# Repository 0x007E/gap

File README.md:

# `GAP` - GamePad (HTLboy)

The `GAP` project is based on a pcb with an [ATmega3208/ATmega4808](#additional-information) and is extended with two [Matrix LED Displays](https://github.com/0x007e/mad). It can be used as controller for games and graphical things. The `GAP` has 8 buttons (1 Cross `[4]`, A & B `[2]`, Select `[1]` and Start `[1]`), 4 LEDs, a potentiometer to control the volume and a built in `UPDI` programmer for the pad itself and the connected displays. Data for displays is sent over `SPI`. The `GAP` also implements a battery controller for [LiPo Batteries](#additional-information). They can be charged over USB. The battery can drive the system for about ~5 hours. There is also a `TWI` interface to load games from an `EEPROM` into the system.

| Experience | Level |
|:------------|:-----:|
| Soldering   |  |
| Mechanical  |  |
| Software    |  |

# Downloads

| Type      | File               | Description              |
|:---------:|:------------------:|:-------------------------|
| Schematic | [pdf](https://github.com/0x007E/gap/releases/latest/download/schematic.pdf) / [cadlab](https://cadlab.io/project/29666/main/files) | Schematic files |
| Board | [pdf](https://github.com/0x007E/gap/releases/latest/download/pcb.pdf) / [cadlab](https://cadlab.io/project/29666/main/files) | Board file |
| Drill | [pdf](https://github.com/0x007E/gap/releases/latest/download/drill.pdf) | Drill file |
| PCB | [zip](https://github.com/0x007E/gap/releases/latest/download/kicad.zip) / [tar](https://github.com/0x007E/gap/releases/latest/download/kicad.tar.gz) | KiCAD/Gerber/BoM/Drill files |
| Mechanical | [zip](https://github.com/0x007E/gap/releases/latest/download/freecad.zip) / [tar](https://github.com/0x007E/gap/releases/latest/download/freecad.tar.gz) | FreeCAD/Housing and PCB (STEP) files     |
| Display Firmware | [zip](https://github.com/0x007E/mad/releases/latest/download/firmware.zip) / [tar](https://github.com/0x007E/mad/releases/latest/download/firmware.tar.gz) | Firmware for ATtiny406/ATtiny1606 (Display) |
| Demo Firmware | [zip](https://github.com/0x007E/gap/releases/latest/download/firmware-demo.zip) / [tar](https://github.com/0x007E/gap/releases/latest/download/firmware-demo.tar.gz) | Test application for ATmega3208/ATmega4808 |

# Hardware

There are two parts of the hardware. The pcb (`GAP` + 2x`MAD`) and the housing. The pcb is created with [KiCAD](#additional-information) and the housing with `FreeCAD`. The software is programmed with [Microchip (Atmel) Studio](#additional-information). All files are built with `github actions` so that they are ready for a production environment. The housing is printed with a 3D-printer (`Dremel 3D40`).

## PCB

The circuit board is populated on both sides (Top, Bottom). The best way for soldering the `SMD` components is within a vapor phase soldering system and for the `THT` components with a standard soldering system.

### Top Layer

### Bottom Layer

## Mechanical

The housing has a tolerance of `0.2mm` on each side of the case. So the pcb should fit perfectly in the housing. The tolerance can be modified with `FreeCAD` in the `Parameter` Spreadsheet.

### Assembled

#### Exploded

# Programming/Setup

For programming the `GAP` is necessary to power the system with `5V` over the USB jack. The `GAP` has an integrated `UPDI` programmer and a pin to select the programming device (`Pad` or `Display`). With Jumper `J3/J4` bridged the [UPDI](#additional-information) programmer is enabled. To program the `Pad` it is necessary to set the Jumper `JP2` between the pins `2-3`. If jumper `JP2` is set between `1-2` the `MAD` display(s) can be programmed (set the jumper `JP1` at the display that should be programmed). The firmware for the `pad`/`display` can be downloaded (see the [download section](#downloads)).

``` bash
#              +---+---+---+---+---+---+  
#          +---+ 1 | 2 | 3 | 4 | 5 | 6 +---+
#          |   +---+---+---+---+---+---+ D |
#          |             S               I |
#          |         U   O               S |
#          |     V   P       S       G   P |
#          |     C   D       C   S   N   L |
#          |     C   I       K   S   D   A |
#        +-+---+         S               Y |
# (*) -> | JP1 |         I                 |
#        +-+---+---+---+---+---+---+---+ 2 |
#          +---+ 1 | 2 | 3 | 4 | 5 | 6 +---+
#              +-+-+-+-+-+-+-+-+-+-+-+-+
#                |   |   |   |   |   |
#              +-+-+-+-+-+-+-+-+-+-+-+-+ 
#          +---+ 1 | 2 | 3 | 4 | 5 | 6 +---+
#          |   +---+---+---+---+---+---+ D |
#          |             S               I |
#          |         U   O               S |
#          |     V   P       S       G   P |
#          |     C   D       C   S   N   L |
#          |     C   I       K   S   D   A |
#        +-+---+         S               Y |
# (*) -> | JP1 |         I                 |
#        +-+---+---+---+---+---+---+---+ 1 |
#          +---+ 1 | 2 | 3 | 4 | 5 | 6 +---+
#              +-+-+-+-+-+-+-+-+-+-+-+-+
#                |   |   |   |   |   |
#              +-+-+-+-+-+-+-+-+-+-+-+-+ 
#          +---+ 1 | 2 | 3 | 4 | 5 | 6 +---+
#          |   +---+---+---+---+---+---+   |
#          |     V   U   M   S   S         |
#          |     C   P   O   C   S         |
#          |     C   D       K             |
#          |         I                  +--+-+
#          |                            |  J +       ---+ Program selected (*) MAD
#          |      G                     |  P +---+   ---+
#          |      A                     |  1 +---+ Program GAP
#          |      M                     +--+-+
#          |      E                        |
#          |      P                        |
#          |      A            SW 11       |
#          |      D        U +---+---+     |
#          |               P | X | X |     |
#          |               D | X | X |     |
#          |               I |   |   |     |
#          |                 +---+---+     |
#          |                     +---+     |
#          | +-------+           | U |     |
#          +-+  TWI  +-----------+ S +-----+
#            +-+++++-+           | B |
#                                +-+-+
#                                  |
#                                  |
#                    +-------------+---------+
#                    |                       |
#                    | +-------------------+ |
#                    | | AVR-Dude/TeraTerm | |
#                    | | ~~~~~~~~          | |
#                    | | ~~~~~             | |
#                    | | ~~~~~~~~~~~~      | |
#                    | |                   | |
#                    | +-------------------+ |
#                    |                       |
#                    | Computer              |
#                    |                       |
#                    +-----------------------+
```

## FUSES

| Register  | Value  |
|:---------:|:------:|
| `APPEND`  | `0x00` |
| `BODCFG`  | `0x00` |
| `BOOTEND` | `0x00` |
| `OSCCFG`  | `0x02` |
| `SYSCFG0` | `0xCC` |
| `SYSCFG1` | `0x00` |
| `WDTCFG`  | `0x00` |

> It is necessary to press the reset button during `avr-dude` is running! Otherwise the `UPDI` programming does not work. Remove Jumper `J3`/`J4` after programming.

## Commands

### Gamepad

``` bash
# With ATmega3208                              !PORT
avrdude.exe -c serialupdi -p m3208 -b 57600 -P COM? -U flash:w:"/path/to/file.hex":a -U eeprom:w:"/path/to/file.eep":a -v

# With ATmega4808                              !PORT
avrdude.exe -c serialupdi -p m4808 -b 57600 -P COM? -U flash:w:"/path/to/file.hex":a -U eeprom:w:"/path/to/file.eep":a -v
```

### Display

``` bash
# With ATtiny406                              !PORT
avrdude.exe -c serialupdi -p t406 -b 57600 -P COM? -U flash:w:"/path/to/file.hex":a -U eeprom:w:"/path/to/file.eep":a -v

# With ATtiny1606                              !PORT
avrdude.exe -c serialupdi -p t1606 -b 57600 -P COM? -U flash:w:"/path/to/file.hex":a -U eeprom:w:"/path/to/file.eep":a -v
```

# Software

The gamepad can be controlled with different libraries to read the input, set the output and control the data on display. An overview of the interfaces are displayed in the [dataflow](#dataflow-diagram) diagram. There is a demo software that is using the libraries to setup and control the gamepad and display (`GAP_LIB`) and a simple game (`GAP_GAME`).

## Dataflow diagram

### Example Library (`matrix.h`)

With the attached demo library (`MAD_LIB`) it is quiet easy to use the display. To setup the matrix display library some `defines` needs to be adjusted.

``` c
// Setup the number of displays that are cascaded in matrix.h
#ifndef MATRIX_DISPLAYS
    #define MATRIX_DISPLAYS 2
#endif
```

``` c
#include "../lib/matrix/matrix.h"

int main(void)
{
    matrix_init();
    matrix_reset();
    _delay_ms(MATRIX_RESET_RECOVERY_TIME_MS);
    matrix_enable();

    matrix_char(1, 'A');
    _delay_ms(1000);
    matrix_char(2, 'B');

    matrix_frame(buffer);
    // ...
}
```

# Additional Information

| Type       | Link               | Description              |
|:----------:|:------------------:|:-------------------------|
| ATtiny406  | [pdf](https://ww1.microchip.com/downloads/en/DeviceDoc/Microchip%208bit%20mcu%20AVR%20ATtiny406%20data%20sheet%2040001976A.pdf) | ATtiny microcontroller |
| ATtiny1606 | [pdf](http://ww1.microchip.com/downloads/en/DeviceDoc/ATtiny806_1606_Data_Sheet_40002029A.pdf) | ATtiny microcontroller |
| ATmega3208 | [pdf](https://ww1.microchip.com/downloads/en/DeviceDoc/ATmega3208-3209-Data-Sheet-DS40002174A.pdf) | Microchip ATmega Datasheet |
| ATmega4808 | [pdf](https://ww1.microchip.com/downloads/en/DeviceDoc/ATmega4808-4809-Data-Sheet-DS40002173A.pdf) | Microchip ATmega Datasheet |
| TA20-11SRWA | [pdf](https://www.kingbrightusa.com/images/catalog/spec/ta20-11srwa.pdf) | Dot Matrix Dispaly |
| Atmel ICE | [pdf](https://ww1.microchip.com/downloads/en/DeviceDoc/Atmel-ICE_UserGuide.pdf) | Atmel ICE datasheet |
| UPDI | [web](https://github.com/0x007e/updi) | UPDI-Adapter with AVR-Dude |
| Microchip Studio | [web](https://www.microchip.com/en-us/tools-resources/develop/microchip-studio) | Download page for Microchip Studio |
| KiCAD | [web](https://www.kicad.org/) | KiCAD project page |
| FreeCAD | [web](https://www.freecad.org/) | FreeCAD project page |
| TeraTerm | [web](https://github.com/TeraTermProject/teraterm/releases/download/v5.3/teraterm-5.3.zip) | Terminal software for UART |

---

R. GAECHTER

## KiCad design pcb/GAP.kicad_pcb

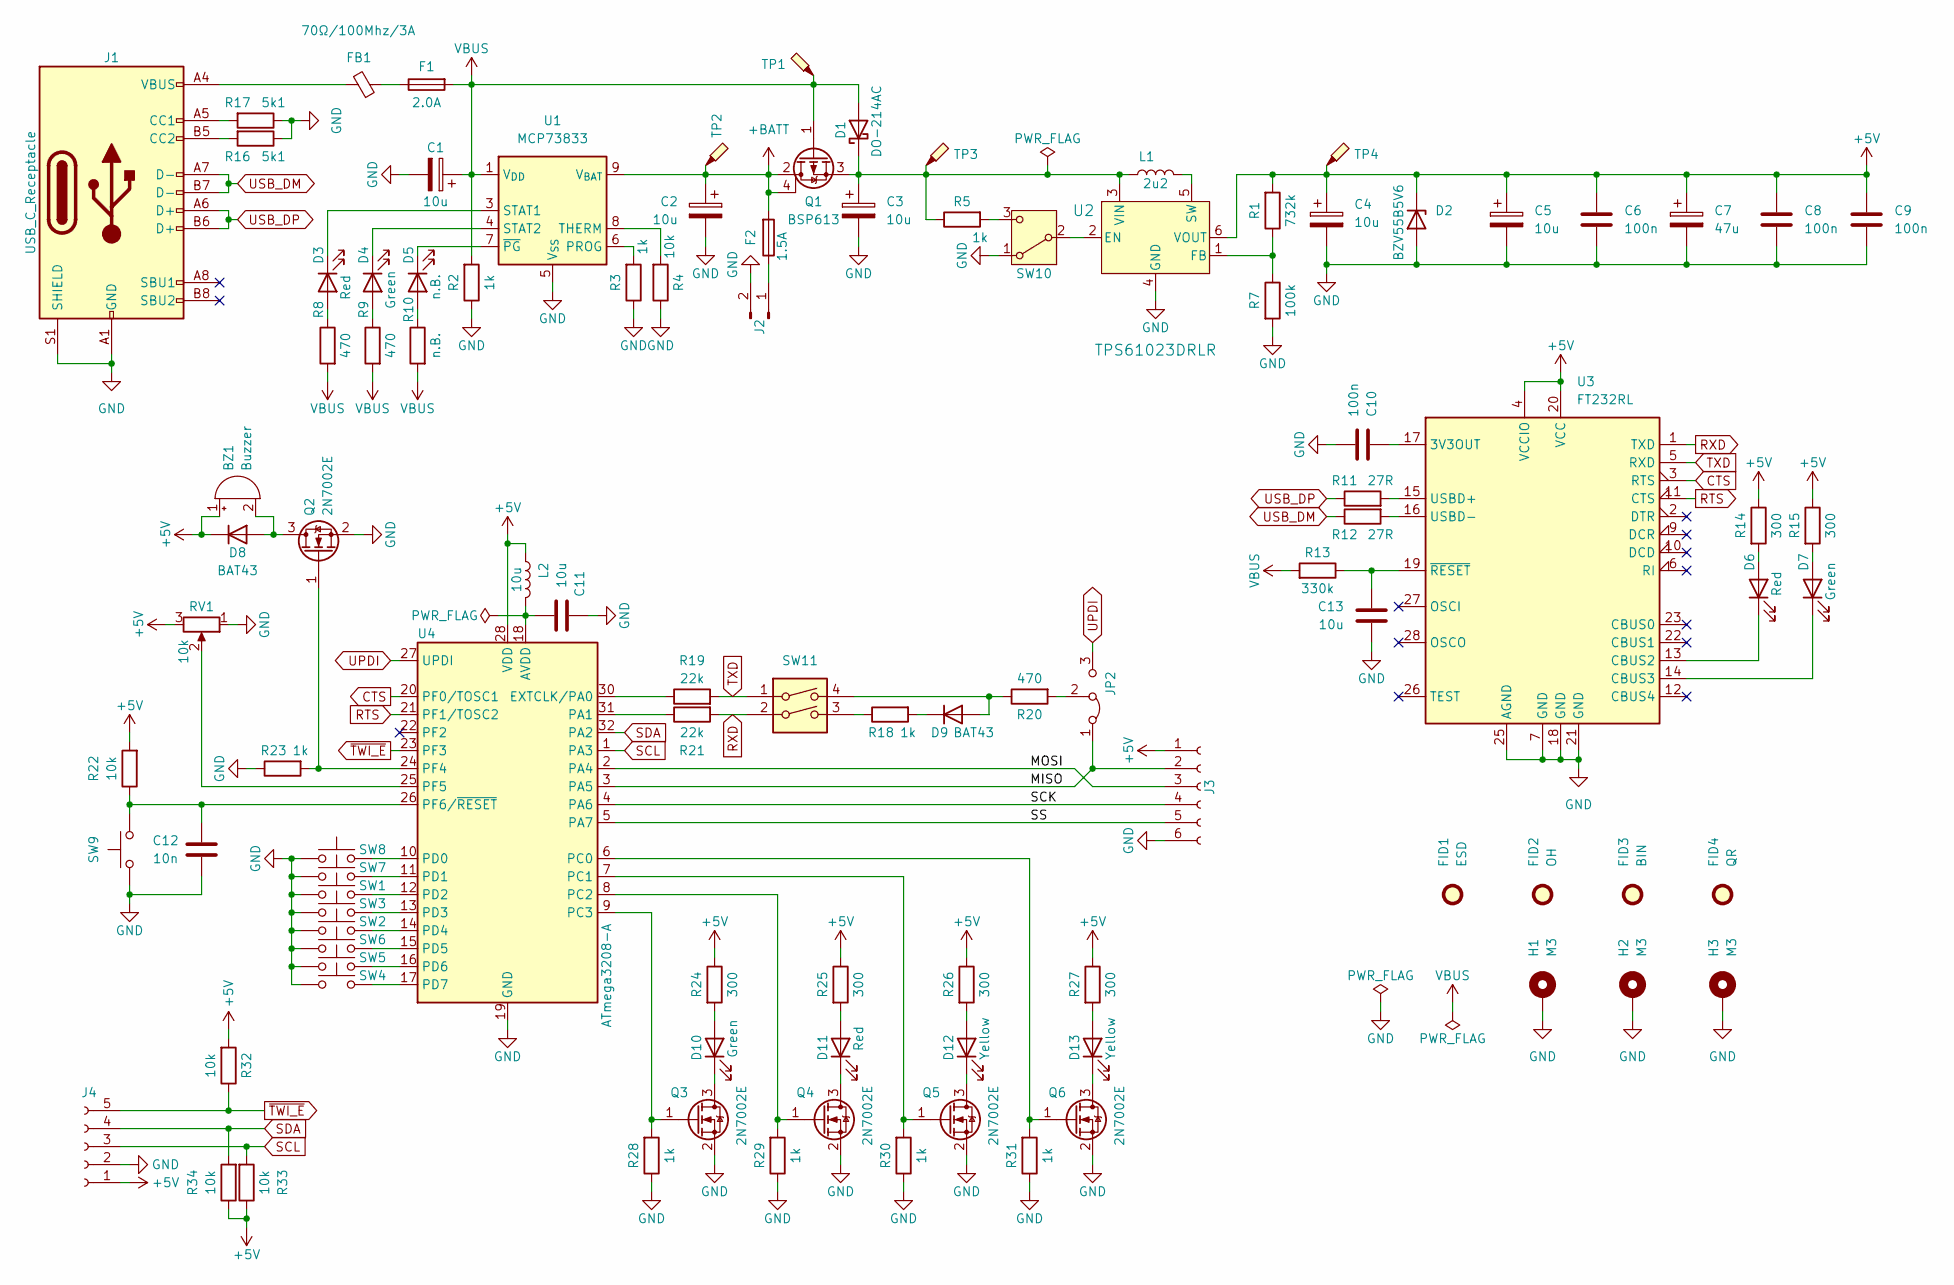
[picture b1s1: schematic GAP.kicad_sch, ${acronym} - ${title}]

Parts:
BZ1: Buzzer; MagneticBuzzer_ProSignal_ABT-410-RC
C1, C2, C3, C4, C5: 10u; CP_EIA-6032-28_Kemet-C
C6, C8, C9, C10: 100n; C_1206_3216Metric
C7: 47u; CP_EIA-6032-28_Kemet-C
C11, C13: 10u; C_1206_3216Metric
C12: 10n; C_1206_3216Metric
D1: DO-214AC; D_SMA
D2: BZV55B5V6; D_MiniMELF
D3, D6, D11: Red; LED_1206_3216Metric
D4, D7, D10: Green; LED_1206_3216Metric
D5: n.B.; LED_1206_3216Metric
D8, D9: BAT43; D_MiniMELF
D12, D13: Yellow; LED_1206_3216Metric
F1: 2.0A; Fuse_1206_3216Metric
F2: 1.5A; Fuse_1206_3216Metric
FB1: 70Ω/100Mhz/3A; L_1206_3216Metric
FID1: ESD; ESD-Logo_6.6x6mm_SilkScreen
FID2: OH; OSHW-Logo_5.7x6mm_SilkScreen
FID3: BIN; WEEE-Logo_4.2x6mm_SilkScreen
FID4: QR; QR_0x007e
H1, H2, H3: M3; MountingHole_3.2mm_M3_DIN965_Pad
J1: USB_C_Receptacle; USB_C_Receptacle_GCT_USB4110
J2: Conn_01x02_Pin; JST_PH_S2B-PH-K_1x02_P2.00mm_Horizontal
J3: Conn_01x06_Socket; PinSocket_1x06_P2.54mm_Horizontal
J4: Conn_01x05_Socket; PinSocket_1x05_P2.54mm_Horizontal
JP2: Jumper_3_Bridged12; PinHeader_1x03_P2.54mm_Horizontal
L1: 2u2; L_Vishay_IFSC-1515AH_4x4x1.8mm
L2: 10u; L_1206_3216Metric
Q1: BSP613; SOT-223
Q2, Q3, Q4, Q5, Q6: 2N7002E; SOT-23
R1: 732k; R_1206_3216Metric
R2, R3, R5, R18, R23, R28, R29, R30, R31: 1k; R_1206_3216Metric
R4, R22, R32, R33, R34: 10k; R_1206_3216Metric
R7: 100k; R_1206_3216Metric
R8, R9, R20: 470; R_1206_3216Metric
R10: n.B.; R_1206_3216Metric
R11, R12: 27R; R_1206_3216Metric
R13: 330k; R_1206_3216Metric
R14, R15, R24, R25, R26, R27: 300; R_1206_3216Metric
R16, R17: 5k1; R_1206_3216Metric
R19, R21: 22k; R_1206_3216Metric
RV1: 10k; Potentiometer_Piher_PT-10-V10_Vertical
SW1, SW2, SW3, SW4, SW5, SW6, SW7, SW8, SW9: SW_Push; SW_SPST_PTS645
SW10: SW_SPDT; SW_SPDT_CK_JS102011SAQN
SW11: SW_DIP_x02; SW_DIP_SPSTx02_Slide_6.7x6.64mm_W8.61mm_P2.54mm_LowProfile
TP1, TP2, TP3, TP4: TestPoint_Probe; TestPoint_Pad_D1.0mm
U1: MCP73833; MSOP-10_3x3mm_P0.5mm
U2: TPS61023DRLR; SOT-563
U3: FT232RL; SSOP-28_5.3x10.2mm_P0.65mm
U4: ATmega3208-A; TQFP-32_7x7mm_P0.8mm

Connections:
+5V: BZ1.1 (+), C4.1, C5.1, C6.1, C7.1, C8.1, C9.1, D2.1 (K), D8.1 (K), J3.1, J4.1, L2.1, R1.2, R14.1, R15.1, R22.2, R24.1, R25.1, R26.1, R27.1, R32.2, R33.1, R34.1, RV1.3, TP4.1, U2.6 (VOUT), U3.4 (VCCIO), U3.20 (VCC), U4.28 (VDD)
+BATT: C2.1, F2.2, Q1.2 (D), Q1.4 (D), TP2.1, U1.9 (V_{BAT}), U1.10 (V_{BAT})
/MISO: J3.2, JP2.1 (A), U4.3 (PA5)
/MOSI: J3.3, U4.2 (PA4)
/SCK: J3.4, U4.4 (PA6)
/SS: J3.5, U4.5 (PA7)
CTS: U3.3 (RTS), U4.20 (PF0/TOSC1)
GND: C1.2, C2.2, C3.2, C4.2, C5.2, C6.2, C7.2, C8.2, C9.2, C10.1, C11.2, C12.2, C13.1, D2.2 (A), H1.1, H2.1, H3.1, J1.A1 (GND), J1.A12 (GND), J1.B1 (GND), J1.B12 (GND), J1.S1 (SHIELD), J2.2, J3.6, J4.2, Q2.2 (S), Q3.2 (S), Q4.2 (S), Q5.2 (S), Q6.2 (S), R2.1, R3.1, R4.1, R7.2, R16.1, R17.1, R23.1, R28.1, R29.1, R30.1, R31.1, RV1.1, SW1.2, SW2.1, SW3.1, SW4.2, SW5.1, SW6.1, SW7.1, SW8.2, SW9.1, SW10.1 (A), U1.5 (V_{SS}), U2.4 (GND), U3.7 (GND), U3.18 (GND), U3.21 (GND), U3.25 (AGND), U4.19 (GND), U4.29 (GND)
unnamed: BZ1.2 (-), D8.2 (A), Q2.3 (D)
unnamed: C3.1, D1.1 (K), L1.1, Q1.3 (S), R5.1, TP3.1, U2.3 (VIN)
unnamed: D3.2 (A), R8.1
unnamed: D3.1 (K), U1.3 (STAT1)
unnamed: D4.2 (A), R9.1
unnamed: D4.1 (K), U1.4 (STAT2)
unnamed: D5.2 (A), R10.1
unnamed: D5.1 (K), U1.7 (~PG)
unnamed: D6.2 (A), R14.2
unnamed: D6.1 (K), U3.13 (CBUS2)
unnamed: D7.2 (A), R15.2
unnamed: D7.1 (K), U3.14 (CBUS3)
unnamed: D9.2 (A), R20.1, SW11.4
unnamed: D9.1 (K), R18.2
unnamed: D10.2 (A), R24.2
unnamed: D10.1 (K), Q3.3 (D)
unnamed: D11.2 (A), R25.2
unnamed: D11.1 (K), Q4.3 (D)
unnamed: D12.2 (A), R26.2
unnamed: D12.1 (K), Q5.3 (D)
unnamed: D13.2 (A), R27.2
unnamed: D13.1 (K), Q6.3 (D)
unnamed: F1.1, FB1.1
unnamed: FB1.2, J1.A4 (VBUS), J1.A9 (VBUS), J1.B4 (VBUS), J1.B9 (VBUS)
unnamed: J1.A5 (CC1), R17.2
unnamed: J1.B5 (CC2), R16.2
unnamed: F2.1, J2.1
unnamed: JP2.2 (C), R20.2
unnamed: Q2.1 (G), R23.2, U4.24 (PF4)
unnamed: Q3.1 (G), R28.2, U4.9 (PC3)
unnamed: Q4.1 (G), R29.2, U4.8 (PC2)
unnamed: Q5.1 (G), R30.2, U4.7 (PC1)
unnamed: Q6.1 (G), R31.2, U4.6 (PC0)
unnamed: R18.1, SW11.3
unnamed: SW10.2 (B), U2.2 (EN)
unnamed: R5.2, SW10.3 (C)
unnamed: R3.2, U1.6 (PROG)
unnamed: R4.2, U1.8 (THERM)
unnamed: R1.1, R7.1, U2.1 (FB)
unnamed: L1.2, U2.5 (SW)
unnamed: C10.2, U3.17 (3V3OUT)
unnamed: R11.2, U3.15 (USBD+)
unnamed: R12.2, U3.16 (USBD-)
unnamed: C13.2, R13.1, U3.19 (~RESET)
unnamed: C11.1, L2.2, U4.18 (AVDD)
unnamed: R19.1, U4.30 (EXTCLK/PA0)
unnamed: R21.1, U4.31 (PA1)
unnamed: SW8.1, U4.10 (PD0)
unnamed: SW7.2, U4.11 (PD1)
unnamed: SW1.1, U4.12 (PD2)
unnamed: SW3.2, U4.13 (PD3)
unnamed: SW2.2, U4.14 (PD4)
unnamed: SW6.2, U4.15 (PD5)
unnamed: SW5.2, U4.16 (PD6)
unnamed: SW4.1, U4.17 (PD7)
unnamed: RV1.2, U4.25 (PF5)
unnamed: C12.1, R22.1, SW9.2, U4.26 (PF6/~RESET)
RTS: U3.11 (CTS), U4.21 (PF1/TOSC2)
RXD: R21.2, SW11.2, U3.1 (TXD)
SCL: J4.3, R33.2, U4.1 (PA3)
SDA: J4.4, R34.2, U4.32 (PA2)
TXD: R19.2, SW11.1, U3.5 (RXD)
UPDI: JP2.3 (B), U4.27 (UPDI)
USB_DM: J1.A7 (D-), J1.B7 (D-), R12.1
USB_DP: J1.A6 (D+), J1.B6 (D+), R11.1
VBUS: C1.1, D1.2 (A), F1.2, Q1.1 (G), R2.2, R8.2, R9.2, R10.2, R13.2, TP1.1, U1.1 (V_{DD}), U1.2 (V_{DD})
~TWI_E: J4.5, R32.1, U4.23 (PF3)

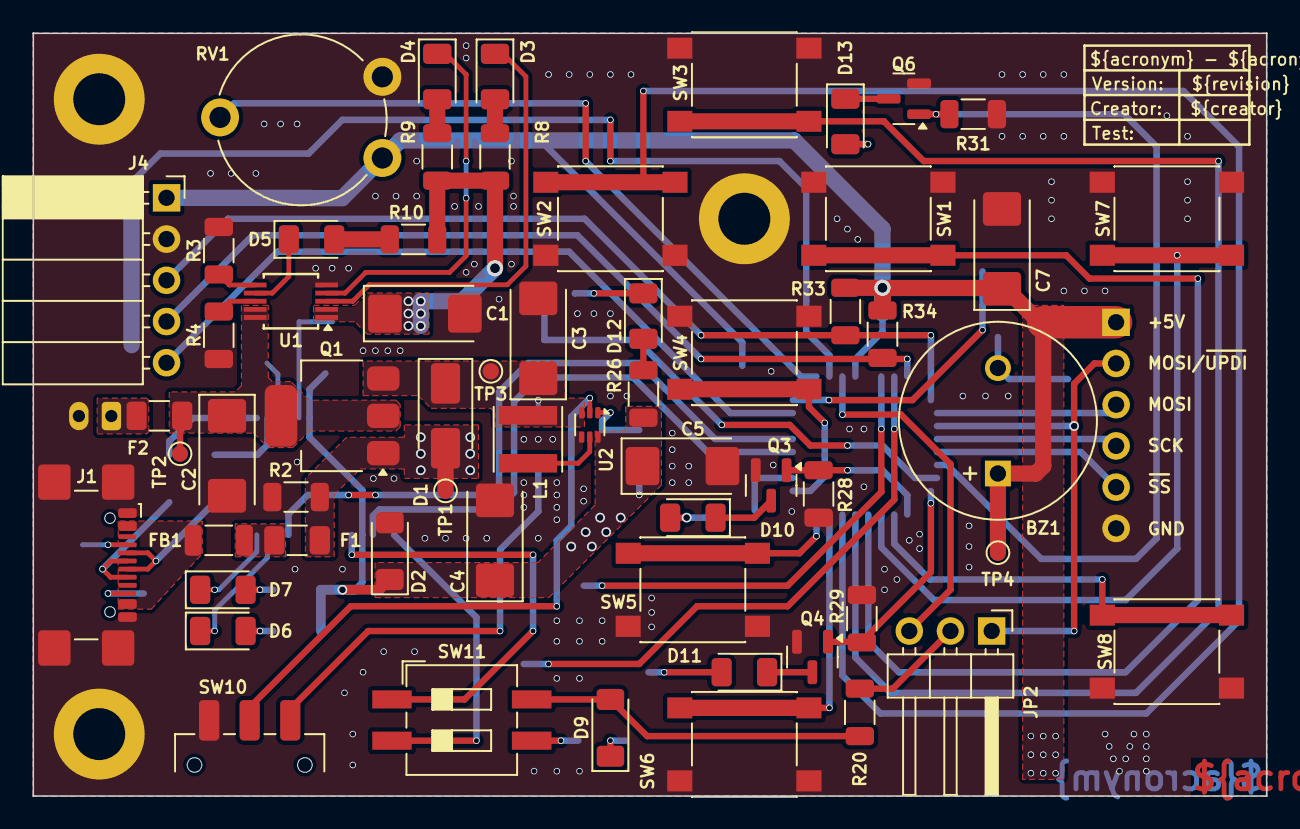
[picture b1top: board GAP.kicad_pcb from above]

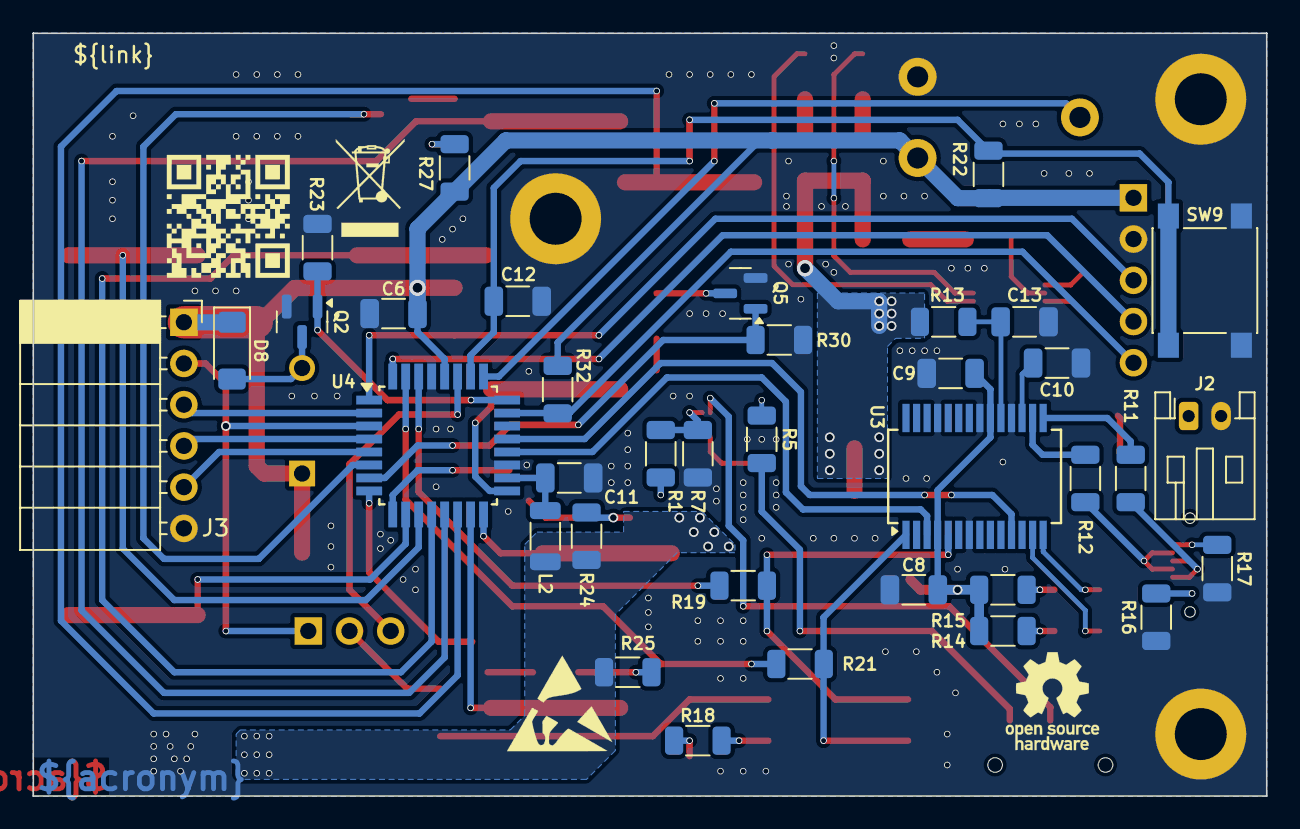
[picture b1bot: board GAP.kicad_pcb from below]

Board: 2 copper layers, 76.0 x 47.0 mm, 103 parts (40 on the bottom side), 75 nets.

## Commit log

2025-10-08 Add mechanical parts
2025-10-08 Add electronical parts
2025-10-08 Add firmware modules
2025-10-08 Add README.md
2025-10-08 Fix cadlab.io link
2025-10-11 Rearrange project structure
2025-10-11 Extend file list
2025-10-11 Add build pipeline
2025-10-11 Fix LICENSE filename
2025-10-11 Change SW10 library
2025-10-11 Update macros to newest DFP
2025-10-11 Fix library path
2025-10-11 Optimize graphics and text
2025-10-12 Add RTS/CTS to UART interface
2025-10-13 Change partlist vendors
2025-10-13 Add release pipeline
2025-10-13 Fix firmware artifact name
2025-10-24 Change firmware pipeline
2025-10-29 Add DeepWiki badge

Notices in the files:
README.md:
License CC By-NC-SA
License GPLv3
parts and their libraries:
license: CC BY-NC-SA 4.0
